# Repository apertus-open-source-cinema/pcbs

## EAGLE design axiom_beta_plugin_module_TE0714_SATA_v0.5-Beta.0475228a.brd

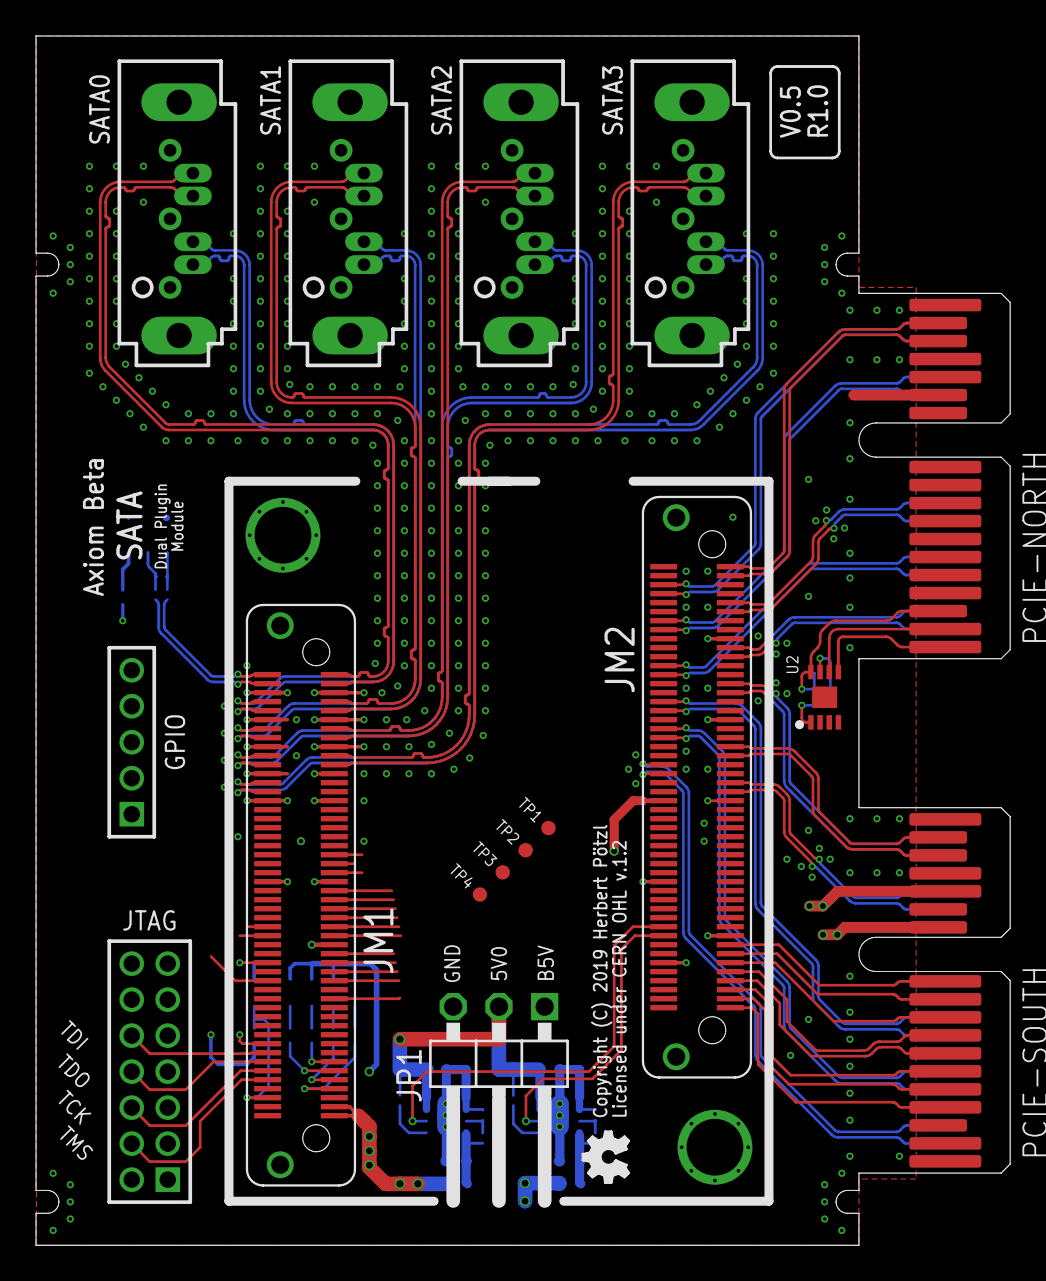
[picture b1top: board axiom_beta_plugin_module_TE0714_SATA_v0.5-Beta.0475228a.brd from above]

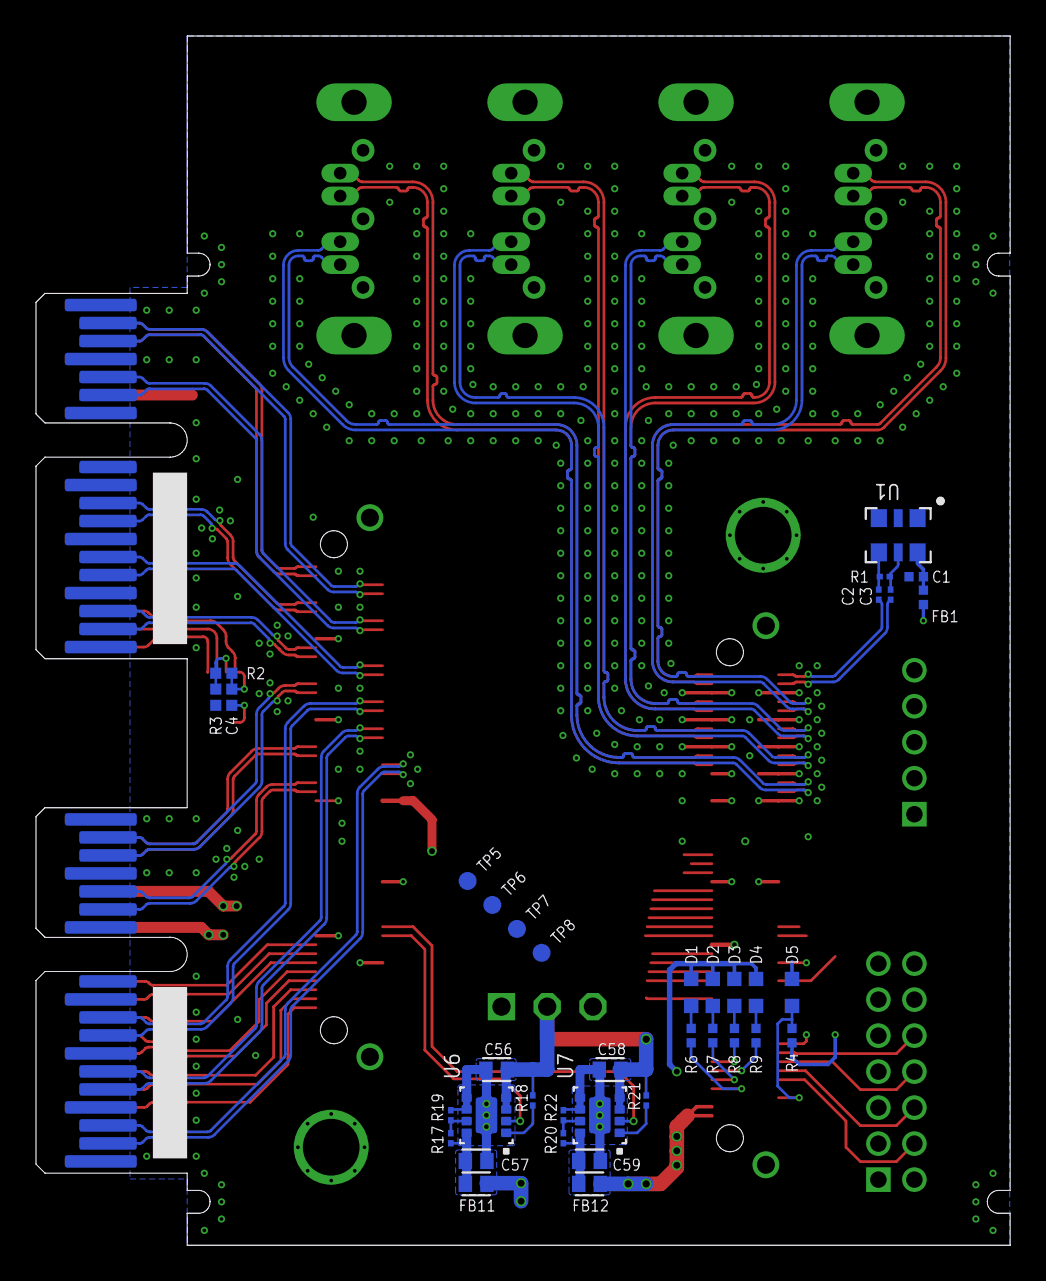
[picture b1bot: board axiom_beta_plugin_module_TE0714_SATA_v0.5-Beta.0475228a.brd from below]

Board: 4 copper layers, 54.1 x 67.2 mm, 54 parts (37 on the bottom side), 93 nets.

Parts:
C1: 470n; 0402-C
C2, C3: 100n; 0201-C
C4: 0402-B
C56, C57, C58, C59: 0603-C
D1, D2, D3, D4, D5: LED; CHIPLED_0603
FB1: 0402-C
FB11, FB12: 0603-C
GPIO: 1X05M
JM1, JM2: LSHM-150-XX.X-XX-DV-A-S
JP1: 1X03/90-S
JTAG: 2X07M
LOGO2: OSHW_LOGO_FILLX0100-NT; OSHW_FILLX100_NOTEXT
PCIE-NORTH: PCIE-36-AXIOM
PCIE-SOUTH: PCIE-36-AXIOM
R1: 100R; 0201-C
R2: 10k; 0402-B
R3: 1k; 0402-B
R4: 5k6; 0402-C
R6, R7, R8, R9: 10k; 0402-C
R17: 200k; 0201-C
R18, R21: 10k; 0201-C
R19, R22: 162k; 0201-C
R20: 510k; 0201-C
SATA0, SATA1, SATA2, SATA3: SATA7-VERT
TP1, TP2, TP3, TP4: TPTP08R; TP08R
TP5, TP6, TP7, TP8: TPTP10R; TP10R
U1: DSC11XX-3.2X2.5; 3.2X2.5
U2: BR24G04NUX; DFN200X300X100-9N
U6, U7: TPS82085; MICROSIP

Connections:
3V3: D1.A, D2.A, D3.A, D4.A, FB1.1, FB12.2, JM1.97, JM1.99, R4.2
B14_L0: JM2.99, PCIE-SOUTH.B4
B14_L11_N: JM2.74, TP1.TP
B14_L11_P: JM2.76, TP2.TP
B14_L12_N: JM2.84, U6.2
B14_L12_P: JM2.82, U7.2
B14_L14_N: JM2.78, TP3.TP
B14_L14_P: JM2.80, TP4.TP
B14_L17_N: JM2.89, PCIE-SOUTH.B9
B14_L17_P: JM2.91, PCIE-SOUTH.B8
B14_L18_N: JM2.85, PCIE-SOUTH.B11
B14_L18_P: JM2.87, PCIE-SOUTH.B10
B14_L19_N: JM2.94, TP6.TP
B14_L19_P: JM2.92, TP5.TP
B14_L20_N: JM2.95, PCIE-SOUTH.B6
B14_L20_P: JM2.93, PCIE-SOUTH.B7
B14_L21_N: JM1.95, U1.1
B14_L21_P: JM1.93, R6.1
B14_L22_N: JM2.96, TP7.TP
B14_L22_P: JM2.98, TP8.TP
B14_L23_N: JM1.89, R9.1
B14_L23_P: JM1.91, R7.1
B14_L24_P: JM1.87, R8.1
B14_L25: JM2.97, PCIE-SOUTH.B5
B15_L1_N: JM2.14, PCIE-NORTH.A14
B15_L1_P: JM2.16, PCIE-NORTH.A13
B15_L5_N: JM2.8, PCIE-NORTH.A16
B15_L5_P: JM2.6, PCIE-NORTH.A17
B15_L6_N: JM2.26, PCIE-NORTH.A5
B15_L6_P: JM2.24, PCIE-NORTH.A6
B15_L7_N: JM2.1, PCIE-NORTH.B17
B15_L7_P: JM2.3, PCIE-NORTH.B16
B15_L10_N: JM2.11, PCIE-NORTH.A8
B15_L10_P: JM2.9, PCIE-NORTH.A9
B15_L12_N: JM2.34, PCIE-SOUTH.A8
B15_L12_P: JM2.32, PCIE-SOUTH.A9
B15_L13_N: JM2.38, PCIE-SOUTH.A6
B15_L13_P: JM2.40, PCIE-SOUTH.A5
B15_L15_N: JM2.19, PCIE-NORTH.A3
B15_L15_P: JM2.21, PCIE-NORTH.A2
B15_L18_N: JM2.27, PCIE-SOUTH.A17
B15_L18_P: JM2.29, PCIE-SOUTH.A16
B15_L19_N: JM2.41, PCIE-SOUTH.B17
B15_L19_P: JM2.43, PCIE-SOUTH.B16
B15_L22_N: JM2.46, PCIE-SOUTH.A3
B15_L22_P: JM2.48, PCIE-SOUTH.A2
B15_L23_N: JM2.51, PCIE-SOUTH.A13
B15_L23_P: JM2.49, PCIE-SOUTH.A14
DONE: D5.A, JM1.96, R4.1
EN_A: R18.1, U6.1
EN_B: R21.1, U7.1
FB_A: R17.1, R19.2, U6.7
FB_B: R20.1, R22.2, U7.7
GND: C1.2, C4.2, C56.2, C57.2, C58.2, C59.2, D5.C, JM1.5, JM1.6, JM1.11, JM1.12, JM1.17, JM1.18, JM1.23, JM1.24, JM1.29, JM1.30, JM1.47, JM1.48, JM1.66, JM1.84, JM1.98, JM1.100, JM1.F1, JM1.F2, JM2.17, JM2.35, JM2.36, JM2.72, JM2.83, JM2.90, JM2.F1, JM2.F2, JP1.3, JTAG.1, JTAG.3, JTAG.5, JTAG.7, JTAG.9, JTAG.11, JTAG.13, PCIE-NORTH.A1, PCIE-NORTH.A4, PCIE-NORTH.A7, PCIE-NORTH.A10, PCIE-NORTH.A12, PCIE-NORTH.A15, PCIE-NORTH.A18, PCIE-NORTH.B15, PCIE-NORTH.B18, PCIE-SOUTH.A1, PCIE-SOUTH.A4, PCIE-SOUTH.A7, PCIE-SOUTH.A10, PCIE-SOUTH.A12, PCIE-SOUTH.A15, PCIE-SOUTH.A18, PCIE-SOUTH.B15, PCIE-SOUTH.B18, R3.2, R19.1, R22.1, SATA0.1, SATA0.4, SATA0.7, SATA1.1, SATA1.4, SATA1.7, SATA2.1, SATA2.4, SATA2.7, SATA3.1, SATA3.4, SATA3.7, U1.3, U2.1, U2.2, U2.3, U2.4, U2.EP, U6.5, U6.6, U6.EP, U7.5, U7.6, U7.EP
I2C_V: C4.1, PCIE-NORTH.B3, R2.1, U2.8
MGT_CLK0_N: C3.2, JM1.4
MGT_CLK0_P: C2.2, JM1.2
MGT_RX0_N: JM1.21, SATA3.5
MGT_RX0_P: JM1.19, SATA3.6
MGT_RX1_N: JM1.15, SATA2.5
MGT_RX1_P: JM1.13, SATA2.6
MGT_RX2_N: JM1.9, SATA1.5
MGT_RX2_P: JM1.7, SATA1.6
MGT_RX3_N: JM1.3, SATA0.5
MGT_RX3_P: JM1.1, SATA0.6
MGT_TX0_N: JM1.28, SATA3.3
MGT_TX0_P: JM1.26, SATA3.2
MGT_TX1_N: JM1.22, SATA2.3
MGT_TX1_P: JM1.20, SATA2.2
MGT_TX2_N: JM1.16, SATA1.3
MGT_TX2_P: JM1.14, SATA1.2
MGT_TX3_N: JM1.10, SATA0.3
MGT_TX3_P: JM1.8, SATA0.2
unnamed: D1.C, R6.2
unnamed: D2.C, R7.2
unnamed: D3.C, R8.2
unnamed: D4.C, R9.2
unnamed: R2.2, R3.1, U2.7
OUT_N: C3.1, R1.2, U1.5
OUT_P: C2.1, R1.1, U1.4
SCL: PCIE-NORTH.B2, U2.6
SDA: PCIE-NORTH.B1, U2.5
S_5V: JP1.1, PCIE-SOUTH.B12
S_VCCIO: JM2.54, PCIE-SOUTH.B14
TCK: JM1.90, JTAG.6
TDI: JM1.86, JTAG.10
TDO: JM1.88, JTAG.8
TMS: JM1.92, JTAG.4
VCCIO0: JM2.53, JTAG.2
VOUT_A: C57.1, FB11.1, R17.2, U6.8
VOUT_B: C59.1, FB12.1, R20.2, U7.8
VSUP: C56.1, C58.1, JP1.2, R18.2, R21.2, U6.3, U6.4, U7.3, U7.4
V_CLK: C1.1, FB1.2, U1.6

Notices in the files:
axiom_beta_plugin_module_TE0714_SATA_v0.5-Beta.0475228a.brd:
Copyright (C) 2019 Herbert Pötzl
Licensed under CERN OHL v.1.2
